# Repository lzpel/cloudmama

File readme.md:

# cloudmama

機械学習で生活習慣改善を支援するAIカメラ。
一人暮らしの大学生・社会人の生活を指導する目でありたい。

Maker Faire Tokyo 2023 (10/14-15 @ビッグサイト) に出展予定。
5月11日（木）～出展作品の受付が始まるので準備を進めている。

## 紹介動画と紹介記事

[動画: Maker Faire Tokyo 2023 出展作品紹介 規則正しい生活を支援するAIカメラ cloudmama](https://vimeo.com/803534490)

[記事: ステイホームで乱れた生活習慣を機械学習を使って改善する話 #kuac2020](https://qiita.com/lzpel/items/e25633684128cebec6b8)

## 作り方

1. [3dmodel/package.stl](./3dmodel/package.stl)を3Dプリンターで印刷します
2. [PCB/LZP32-SPEAKER_(最新版)](./PCB)をPCB製造業者（例えばSeeeds Fusion, PCBWAY）などで製造してもらいます。
    - BOMに従い部品も実装してください
3. スピーカー（F02607H0）（[秋月電子](https://akizukidenshi.com/catalog/g/gP-10366/)）を購入してください
    - これでなくとも大抵の8ohmスピーカーに対応しています、別のスピーカーを用いる場合は自分で外装を設計してください。
4. スピーカーの+/-を発注した基盤の+/-にスクリューターミナルを用いて接続してください。
6. USB給電すれば動作します。
7. Wifiから設定画面に接続します。
    - TODO: 以下完成させる、プロトタイピングとしては動くが配布できる状態ではない

## 開発ノウハウ

- esp-idf5.0のwindows版 をインストールして組み込みプログラミングを行う
  - docker image版の開発環境は仮想環境からUSBを経由してボードに書き込めないので使えない
- スピーカーと接続する screw terminal の部品選定について
  - KF350-3.5-2P  採用
  - DB125-3.5-2P-GN-S　　不採用　在庫が少ないので依存するのは良くない
- Fusion360による基板設計での頻出問題と解決法
  - 部品の3Dモデルが反映されない
    - 3Dモデルにstlを使っている->体積を持たないので使えません（警告マークが出ているはずです）STEPファイルを使いましょう
    - STEPファイルを読み込めない->メッシュとしては読み込めません->Teamの一ファイルとしてアップロードし、それを外部コンポーネントとして挿入しましょう（ドラッグアンドドロップ）
    - 3Dモデルが更新されていない->基盤デザインで「ライブラリからデザインを更新」をクリック、「デザインで使用されている全てのライブラリからデザインを更新」ボタンは効果がない->3DPCBにプッシュ

## License

MIT Copyright 2020 lzpel

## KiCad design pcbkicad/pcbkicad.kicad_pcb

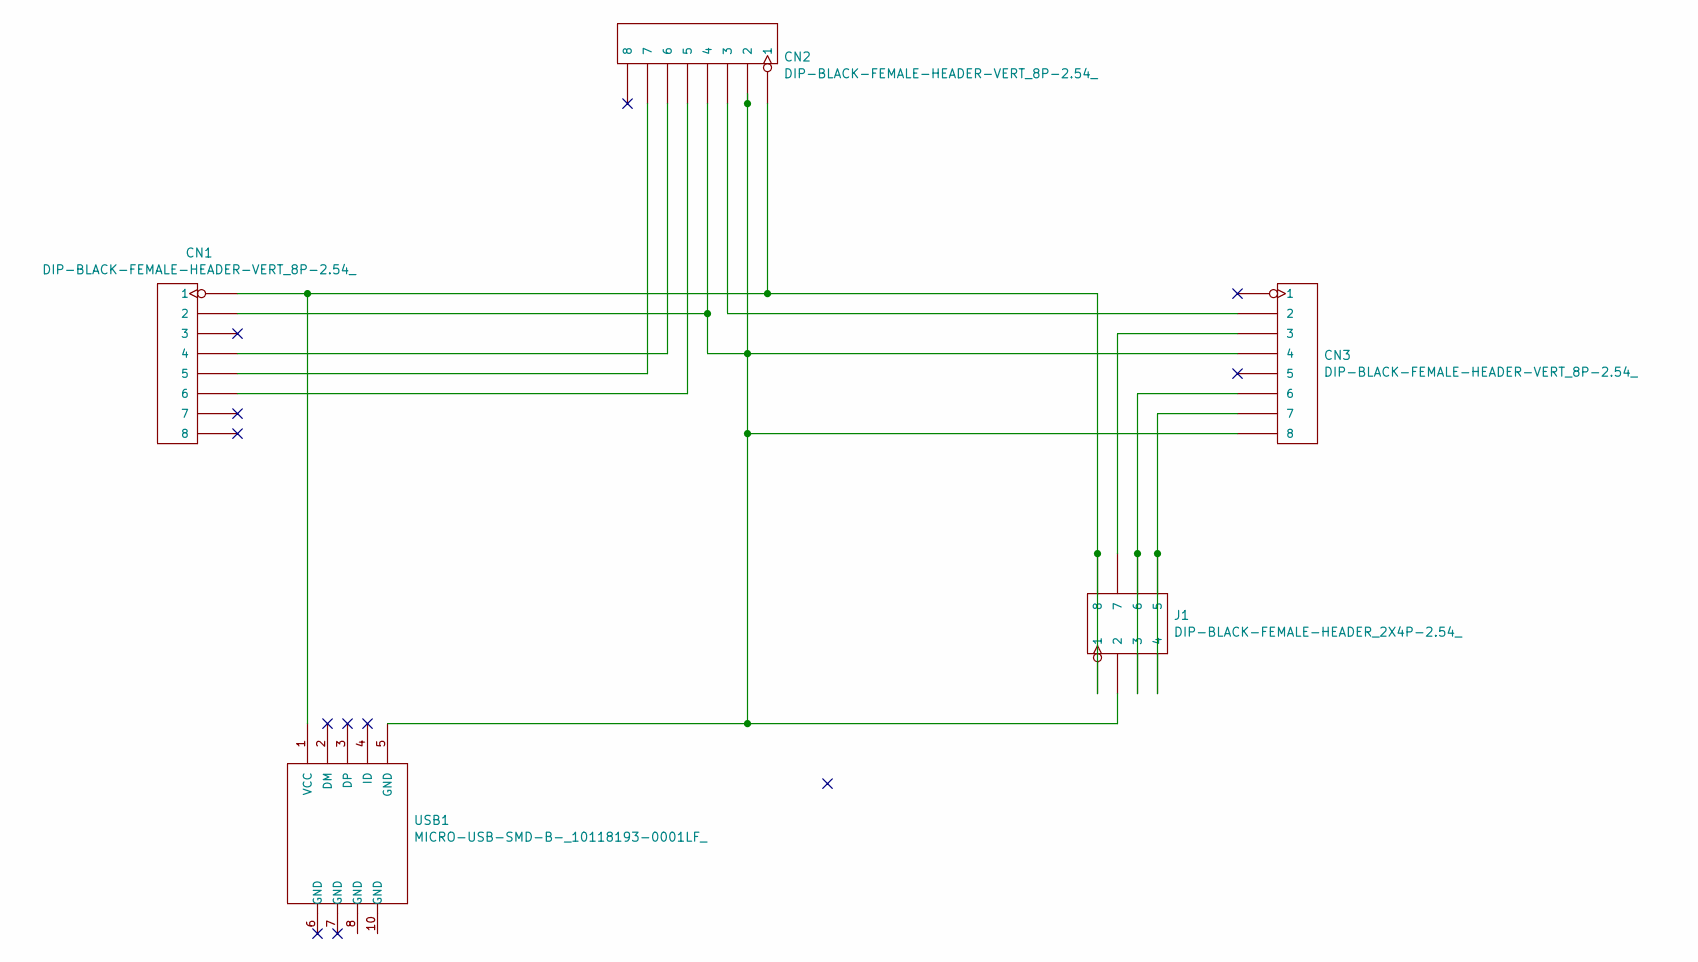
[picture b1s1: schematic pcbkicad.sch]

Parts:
CN1, CN2, CN3: DIP-BLACK-FEMALE-HEADER-VERT_8P-2.54_; H8-2.54; MPN F185-1108A1BSYC1
J1: DIP-BLACK-FEMALE-HEADER_2X4P-2.54_; H2X4-2.54
USB1: MICRO-USB-SMD-B-_10118193-0001LF_; MICRO-USB5+6P-SMD-0.65-B; MPN 10118193-0001LF

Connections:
unnamed: CN1.1, CN2.1, J1.1, J1.8, USB1.1 (VCC)
unnamed: CN1.2, CN2.2, CN2.4, CN3.4, CN3.8, J1.2, USB1.5 (GND)
unnamed: CN1.4, CN2.6
unnamed: CN1.5, CN2.7
unnamed: CN1.6, CN2.5
unnamed: CN2.3, CN3.2
unnamed: CN3.3, J1.7
unnamed: CN3.6, J1.3, J1.6
unnamed: CN3.7, J1.4, J1.5
unnamed: USB1.8 (GND), USB1.9 (GND)
unnamed: USB1.10 (GND), USB1.11 (GND)

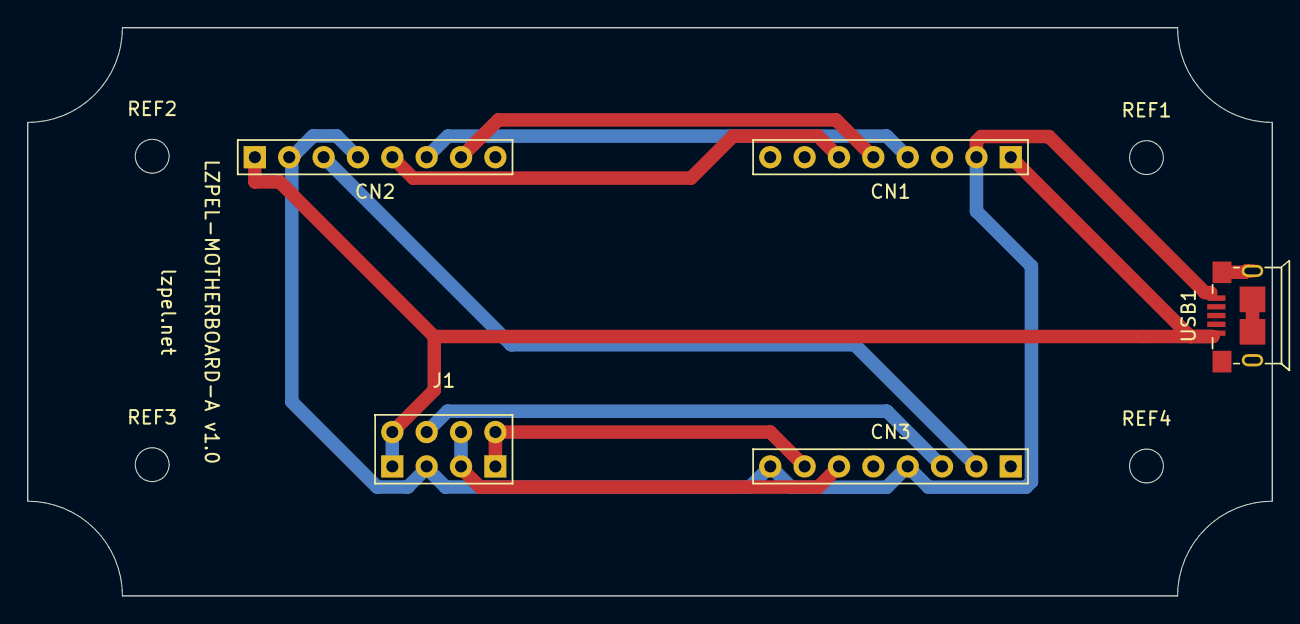
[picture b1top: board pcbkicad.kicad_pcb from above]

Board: 2 copper layers, 92.0 x 42.0 mm, 9 parts (0 on the bottom side), 11 nets.

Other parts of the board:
REF1, REF2, REF3, REF4: MountingHole_2.5mm

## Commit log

2020-05-01 complete prototype
2020-10-08 Update Text
2020-10-08 Use Nanoseconds() in stead of Milliseconds()
2020-12-10 test
2020-12-11 判定以外完成
2021-10-09 espidf
2021-11-21 FusionPCB
2022-03-13 esp8266-google-home-notifier
2022-04-10 update wifi ssid password
2022-12-29 esp-idf
2022-12-29 copy url sample
2022-12-29 nosignal
2022-12-30 右側GNDえぐり取ったら音が鳴った
2023-01-05 trivial
2023-01-06 import code but still noisy
2023-01-06 add hardwae
2023-01-08 readme
2023-01-09 audio
2023-01-09 project build complete
2023-03-03 add 3d model
2023-03-03 update google_app_engine and mircrosd
2025-08-09 Latest snapshot only
2025-08-09 confirm work
